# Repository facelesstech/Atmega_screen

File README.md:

Atmega_screen
=============

LCD status screen powered by Atmega328

Blog post can be found here 

https://facelesstech.wordpress.com/2014/10/14/atmega_screen-lcd-status-screen-with-a-few-bells-and-whiles-new/

Atmega_screen video here

http://youtu.be/g3aH3pATusc?list=UUuK2SlZlnsWDYSvBv1lbuAw

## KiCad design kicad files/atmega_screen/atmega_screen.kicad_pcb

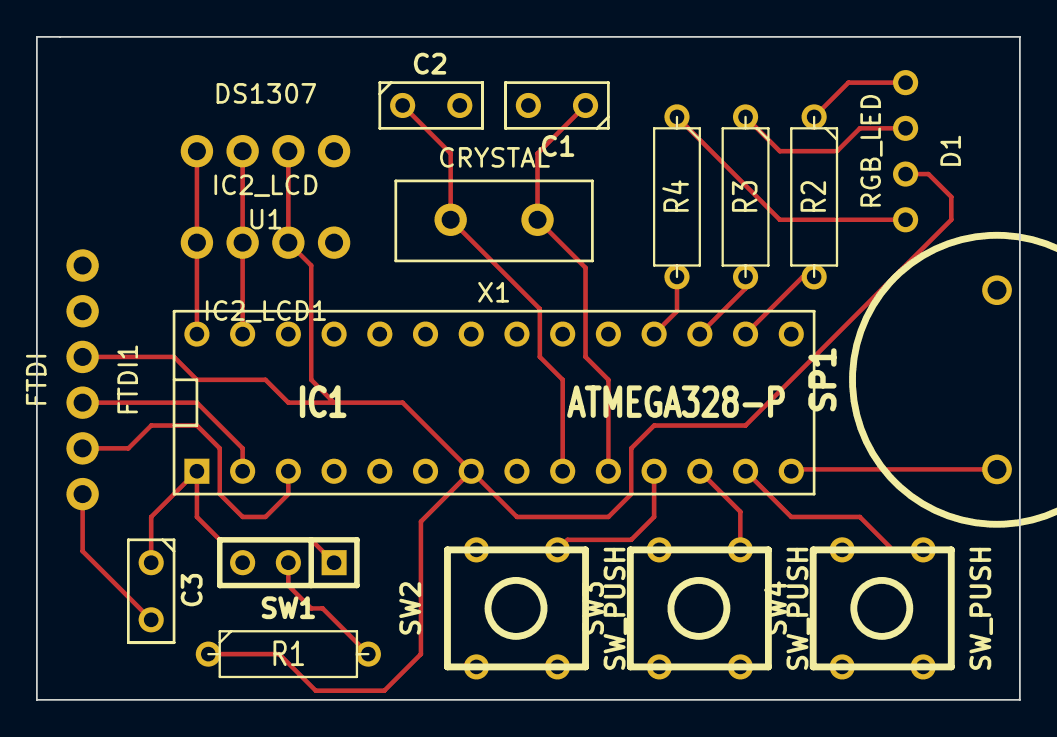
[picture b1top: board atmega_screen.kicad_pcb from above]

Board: 2 copper layers, 54.6 x 36.8 mm, 18 parts (0 on the bottom side), 21 nets.

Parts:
C1, C2, C3: 10; C_3mm
D1: RGB_LED; RGB_LED_Anode
FTDI1: FTDI; FTDI_Board
IC1: ATMEGA328-P; DIP-28_Socket
IC2_LCD1: IC2_LCD; IC2_LED
R1: 120; R3-5
R2, R3, R4: 220; R3-5
SP1: SPEAKER; Piezo_buzz_TH
SW1: SWITCH_INV; MICROSWITCH_SPST
SW2, SW3, SW4: SW_PUSH; SW_PUSH_SMALL_OBR
U1: DS1307; IC2_DS1307
X1: CRYSTAL; CRYSTAL_A_S

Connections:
unnamed: FTDI1.5, IC1.3
unnamed: IC1.28, IC2_LCD1.4, U1.4
unnamed: R1.2, SW1.2
unnamed: IC1.14, SP1.2
unnamed: IC1.18, R4.2
unnamed: C1.2, C2.2, FTDI1.1, IC1.8, IC2_LCD1.1, SP1.1, SW2.1, SW3.1, SW4.1, U1.1
unnamed: C3.2, FTDI1.6
unnamed: IC1.27, IC2_LCD1.3, U1.3
unnamed: IC1.11, SW2.2
unnamed: IC1.12, SW3.2
unnamed: IC1.13, SW4.2
unnamed: D1.1, R2.1
unnamed: D1.2, R3.1
unnamed: IC1.16, R2.2
unnamed: IC1.17, R3.2
unnamed: C3.1, IC1.1, SW1.1
unnamed: FTDI1.4, IC1.2
unnamed: D1.3, FTDI1.3, IC1.7, IC2_LCD1.2, R1.1, U1.2
unnamed: C2.1, IC1.9, X1.2
unnamed: C1.1, IC1.10, X1.1
unnamed: D1.4, R4.1

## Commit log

2014-06-16 Stock ticker to disply stock info from yahoo
2014-06-16 display weather from API
2014-06-18 Rename atmega_screen_stock_ticker.py to python-scrips/atmega_screen_stock_ticker.py
    moved to folder
2014-06-18 Rename atmega_screen_weather.py to python-scrips/atmega_screen_weather.py
2014-06-18 Rename python-scrips/atmega_screen_stock_ticker.py to stock-ticker/atmega_screen_stock_ticker.py
2014-06-18 Rename python-scrips/atmega_screen_weather.py to weather/atmega_screen_weather.py
2014-06-18 arduino code
2014-06-18 ardiuno code
2014-07-03 kicad files
2014-07-03 Create arduino_python_files
2014-07-04 changed folder names
2014-07-04 updated code
2014-07-04 new code
2014-07-04 Added code
2014-07-07 Added comments to the code
2014-07-07 Added comments to my code
2014-07-08 commented code
2014-07-10 added custom char to LCD
2014-07-12 added backlight toggle
2014-07-14 Toggle RGB LED with bottom red button
2014-07-14 Toggle lcd backlight code added
2014-07-14 Code change
2014-07-14 comments added
2014-07-15 WIP magic 8 ball with splash screen
2014-07-16 Code re-write and bug fixes
2014-07-17 Beep on button press and added comments
2014-07-20 easier to read
2014-07-20 commeted and clean or API keys
2014-07-20 Currency ticker for #atmega_screen rev 1
2014-07-26 Added colour change RGB with temp into python and arduino code
2014-07-26 clean up code change -bug fix
2014-07-26 added more RGB colours to the temp
2014-07-27 Fixed RGB LED wasnt turning on between 15 and 20 degress
2014-07-27 fixed comments
2014-07-27 fixed the splash screen
2014-07-27 added splash screen
2014-07-28 refined the splash screen
2014-07-28 changed pound sign to dollar and added splash screen
2014-07-28 refined the splash screen made it pretty
2014-08-09 added GPL v3 licence
2014-11-12 changed the name of the folder
2014-11-12 removed old folder
2014-11-12 changed folder name
2014-11-14 fixed bugs with button code
2014-11-15 Added blog post URL
2014-11-15 added video URL
2014-11-15 Breadboard layout
